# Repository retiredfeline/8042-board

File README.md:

# 8042 MCU board

These are the Kicad design files for the 8042 controller board used in my projects published at Hackaday, including [8042 clock](https://hackaday.io/project/161909-8042-clock)

## Versioning

First release November 2018

Update November 2019

## Authors

* **Ken Yap**

## License

See the [LICENSE](LICENSE.md) file for license rights and limitations (MIT).

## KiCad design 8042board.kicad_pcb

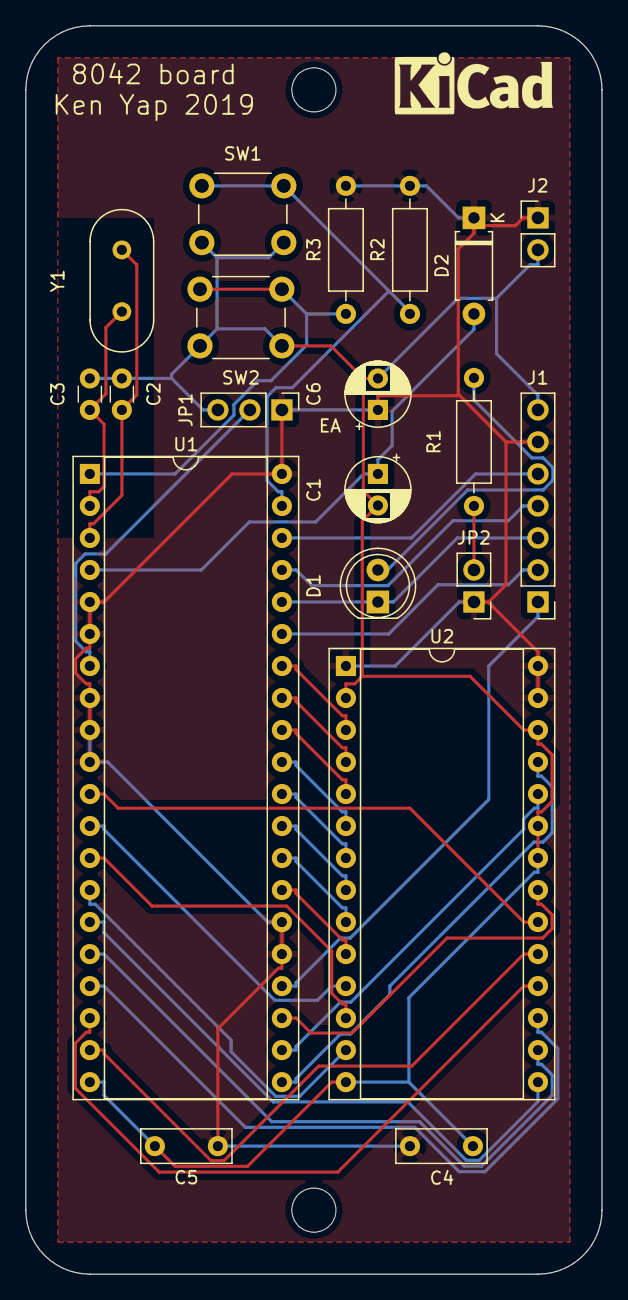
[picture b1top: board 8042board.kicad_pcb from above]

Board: 2 copper layers, 45.7 x 99.1 mm, 22 parts (0 on the bottom side), 35 nets.

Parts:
C1: 1uF; CP_Radial_D5.0mm_P2.50mm
C2, C3: 22pF; C_Disc_D3.0mm_W1.6mm_P2.50mm
C4, C5: 0.1uF; C_Rect_L7.0mm_W2.5mm_P5.00mm
C6: 10uF; CP_Radial_D5.0mm_P2.50mm
D1: Blink; LED_D5.0mm
D2: 1N4148; D_A-405_P7.62mm_Horizontal
H1, H2: MountingHole; MountingHole_3.5mm
J1: To TM1637 display; PinHeader_1x07_P2.54mm_Vertical
J2: Power; PinHeader_1x02_P2.54mm_Vertical
JP1: ROM; PinHeader_1x03_P2.54mm_Vertical
JP2: LED; PinHeader_1x02_P2.54mm_Vertical
R1: 1k; R_Axial_DIN0207_L6.3mm_D2.5mm_P10.16mm_Horizontal
R2, R3: 22k; R_Axial_DIN0207_L6.3mm_D2.5mm_P10.16mm_Horizontal
SW1: Hour; SW_PUSH_6mm_H4.3mm
SW2: Min; SW_PUSH_6mm_H4.3mm
U1: 8042; DIP-40_W15.24mm_Socket
U2: 27128; DIP-28_W15.24mm_Socket
Y1: 6/12MHz; Crystal_HC18-U_Vertical

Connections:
+5V: C4.1, C5.1, C6.1, D2.1, J1.6, J2.1, JP1.1, JP2.1, R2.1, R3.1, U1.5, U1.6, U1.8, U1.9, U1.10, U1.25, U1.26, U1.40, U2.1, U2.27, U2.28
/A0: U1.27, U2.10
/A1: U1.28, U2.9
/A2: U1.29, U2.8
/A3: U1.30, U2.7
/A4: U1.31, U2.6
/A5: U1.32, U2.5
/A6: U1.33, U2.4
/A7: U1.34, U2.3
/A8: U1.21, U2.25
/A9: U1.22, U2.24
/A10: U1.23, U2.21
/D0: U1.12, U2.11
/D1: U1.13, U2.12
/D2: U1.14, U2.13
/D3: U1.15, U2.15
/D4: U1.16, U2.16
/D5: U1.17, U2.17
/D6: U1.18, U2.18
/D7: U1.19, U2.19
GND: C1.2, C2.2, C3.2, C4.2, C5.2, C6.2, J1.7, J2.2, JP1.3, SW1.2, SW2.1, U1.20, U2.2, U2.14, U2.22, U2.23, U2.26
unnamed: C1.1, D2.2, U1.4
unnamed: C2.1, U1.3, Y1.1
unnamed: C3.1, U1.2, Y1.2
unnamed: D1.1, J1.3, U1.36
unnamed: D1.2, R1.2
unnamed: J1.1, U1.24
unnamed: J1.2, U1.35
unnamed: J1.4, U1.37
unnamed: J1.5, U1.38
unnamed: JP1.2, U1.7
unnamed: JP2.2, R1.1
unnamed: R2.2, SW1.1, U1.39
unnamed: R3.2, SW2.2, U1.1
unnamed: U1.11, U2.20

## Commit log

2018-10-31 1.0 Release
2019-10-18 Update design files, provide Gerber fab files
